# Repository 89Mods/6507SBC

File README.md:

# 6507SBC

A 6507-based single-board computer with 128 bytes RAM, 7KiB ROM, I/O, graphics and sound. As an added challenge, it was built with the requirement to not contain any IC larger than DIP-28.

`Hardware` contains the KiCad project files for the SBC itself, as well as the adapter board for the supported SPI peripherals.

`Programs` are programs written to test various features of the SBC.

`Verilog` contains a basic Verilog implementation of the 6507, and the pixel LCD peripheral. Used during software development when ROM swapping became too tedious. Doesn’t implement undocumented instructions or decimal mode.

For more information, see the writeup [on my website](https://tholin.dev/6507/).

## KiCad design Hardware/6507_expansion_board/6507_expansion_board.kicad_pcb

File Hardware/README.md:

# Hardware

Here are the KiCad projects for the computer! BOMs and Gerbers are in the respective 'production' folder of each KiCad project.

The 'expansion board' is a board that plugs directly into a header on the SBC, and adapts some of its I/O ports to two supported SPI peripherals, which can then be driven in software. One is a 25Qxx flash ROM for additional data storage (7KiB isn’t a lot), and the other a pixel LCD (ST7565), which forms the graphics output of the computer.

They can be found for cheap on AliExpress. I got [this one](https://aliexpress.com/item/1005001621784395.html).

However, in the absence of this, the SBC also has a header for a regular character LCD. If this is not required, components J5, RV1 and R19 can be omitted.

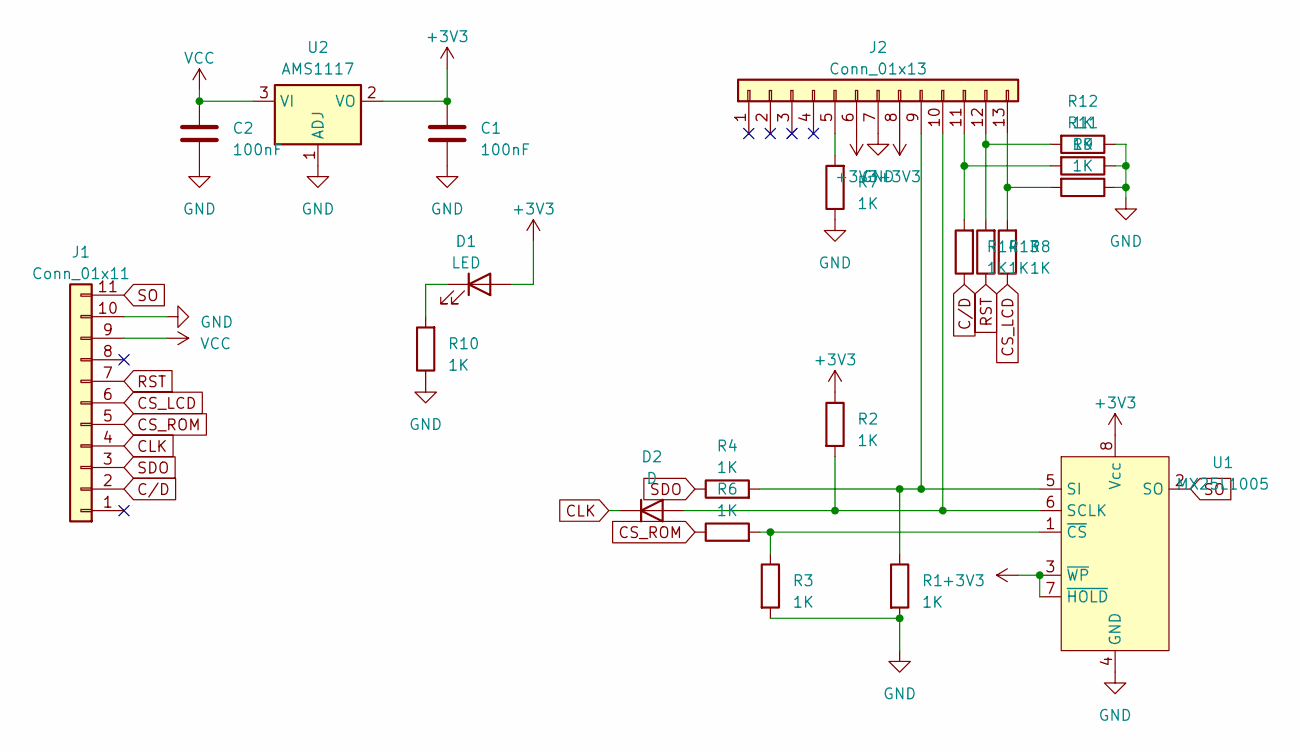
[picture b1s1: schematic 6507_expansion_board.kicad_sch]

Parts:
C1, C2: 100nF; C_1206_3216Metric
D1: LED; LED_0805_2012Metric
D2: D; D_0805_2012Metric
J1: Conn_01x11; PinHeader_1x11_P2.54mm_Vertical
J2: Conn_01x13; PinHeader_1x13_P2.54mm_Vertical
R1, R2, R3, R4, R6, R7, R8, R9, R10, R11, R12, R13, R14: 1K; R_2010_5025Metric_Pad1.40x2.65mm_HandSolder
U1: MX25L1005; DIP-8_W7.62mm_LongPads
U2: AMS1117; SOT-223-3_TabPin2

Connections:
+3V3: C1.1, D1.2 (A), J2.6, J2.8, R2.1, U1.3 (~WP), U1.7 (~HOLD), U1.8 (Vcc), U2.2 (VO)
CLK: D2.1 (K), J1.4
CS_LCD: J1.6, R8.1
CS_ROM: J1.5, R6.1
C/D: J1.2, R14.1
GND: C1.2, C2.2, J1.10, J2.7, R1.2, R3.2, R7.1, R9.1, R10.1, R11.1, R12.1, U1.4 (GND), U2.1 (ADJ)
unnamed: D1.1 (K), R10.2
unnamed: D2.2 (A), J2.10, R2.2, U1.6 (SCLK)
unnamed: J2.5, R7.2
unnamed: J2.9, R1.1, R4.2, U1.5 (SI)
unnamed: J2.11, R11.2, R14.2
unnamed: J2.12, R12.2, R13.2
unnamed: J2.13, R8.2, R9.2
unnamed: R3.1, R6.2, U1.1 (~CS)
RST: J1.7, R13.1
SDO: J1.3, R4.1
SO: J1.11, U1.2 (SO)
VCC: C2.1, J1.9, U2.3 (VI)

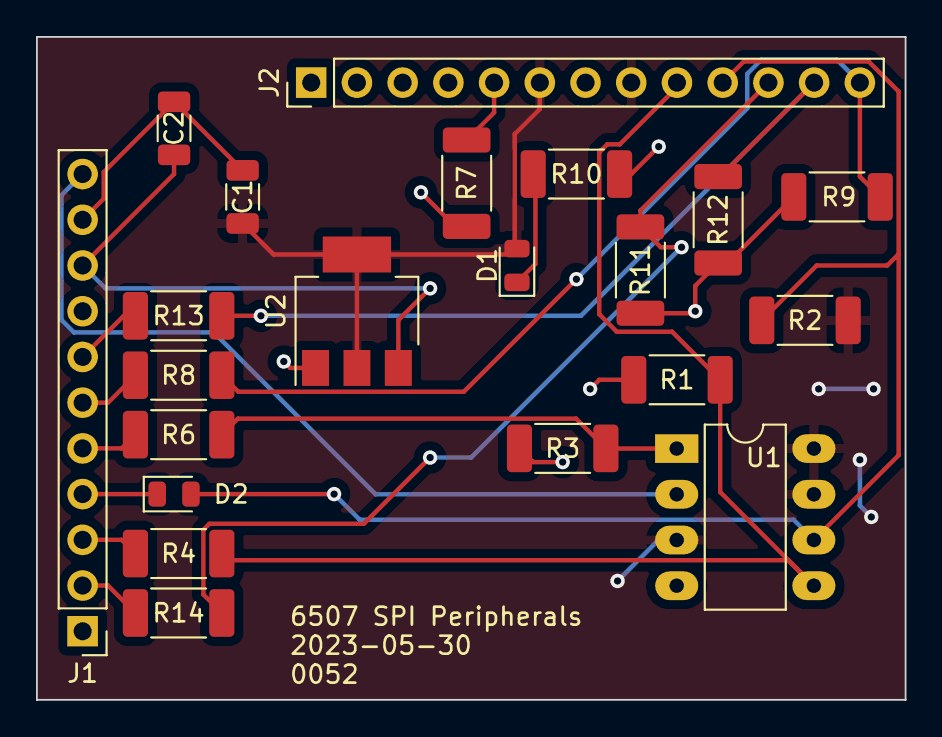
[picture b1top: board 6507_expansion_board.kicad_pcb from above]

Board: 2 copper layers, 48.3 x 36.8 mm, 21 parts (0 on the bottom side), 18 nets.

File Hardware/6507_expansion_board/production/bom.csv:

Designator,Footprint,Quantity,Value,LCSC Part #
C1,1206,1,100nF,
C2,1206,1,100nF,
D1,0805,1,LED,
D2,0805,1,D,
J1,PinHeader_1x11_P2.54mm_Vertical,1,Conn_01x11,
J2,PinHeader_1x13_P2.54mm_Vertical,1,Conn_01x13,
R1,2010,1,1K,
R10,2010,1,1K,
R11,2010,1,1K,
R12,2010,1,1K,
R13,2010,1,1K,
R14,2010,1,1K,
R2,2010,1,1K,
R3,2010,1,1K,
R4,2010,1,1K,
R6,2010,1,1K,
R7,2010,1,1K,
R8,2010,1,1K,
R9,2010,1,1K,
U1,DIP-8_W7.62mm_LongPads,1,MX25L1005,
U2,SOT-223-3_TabPin2,1,AMS1117,

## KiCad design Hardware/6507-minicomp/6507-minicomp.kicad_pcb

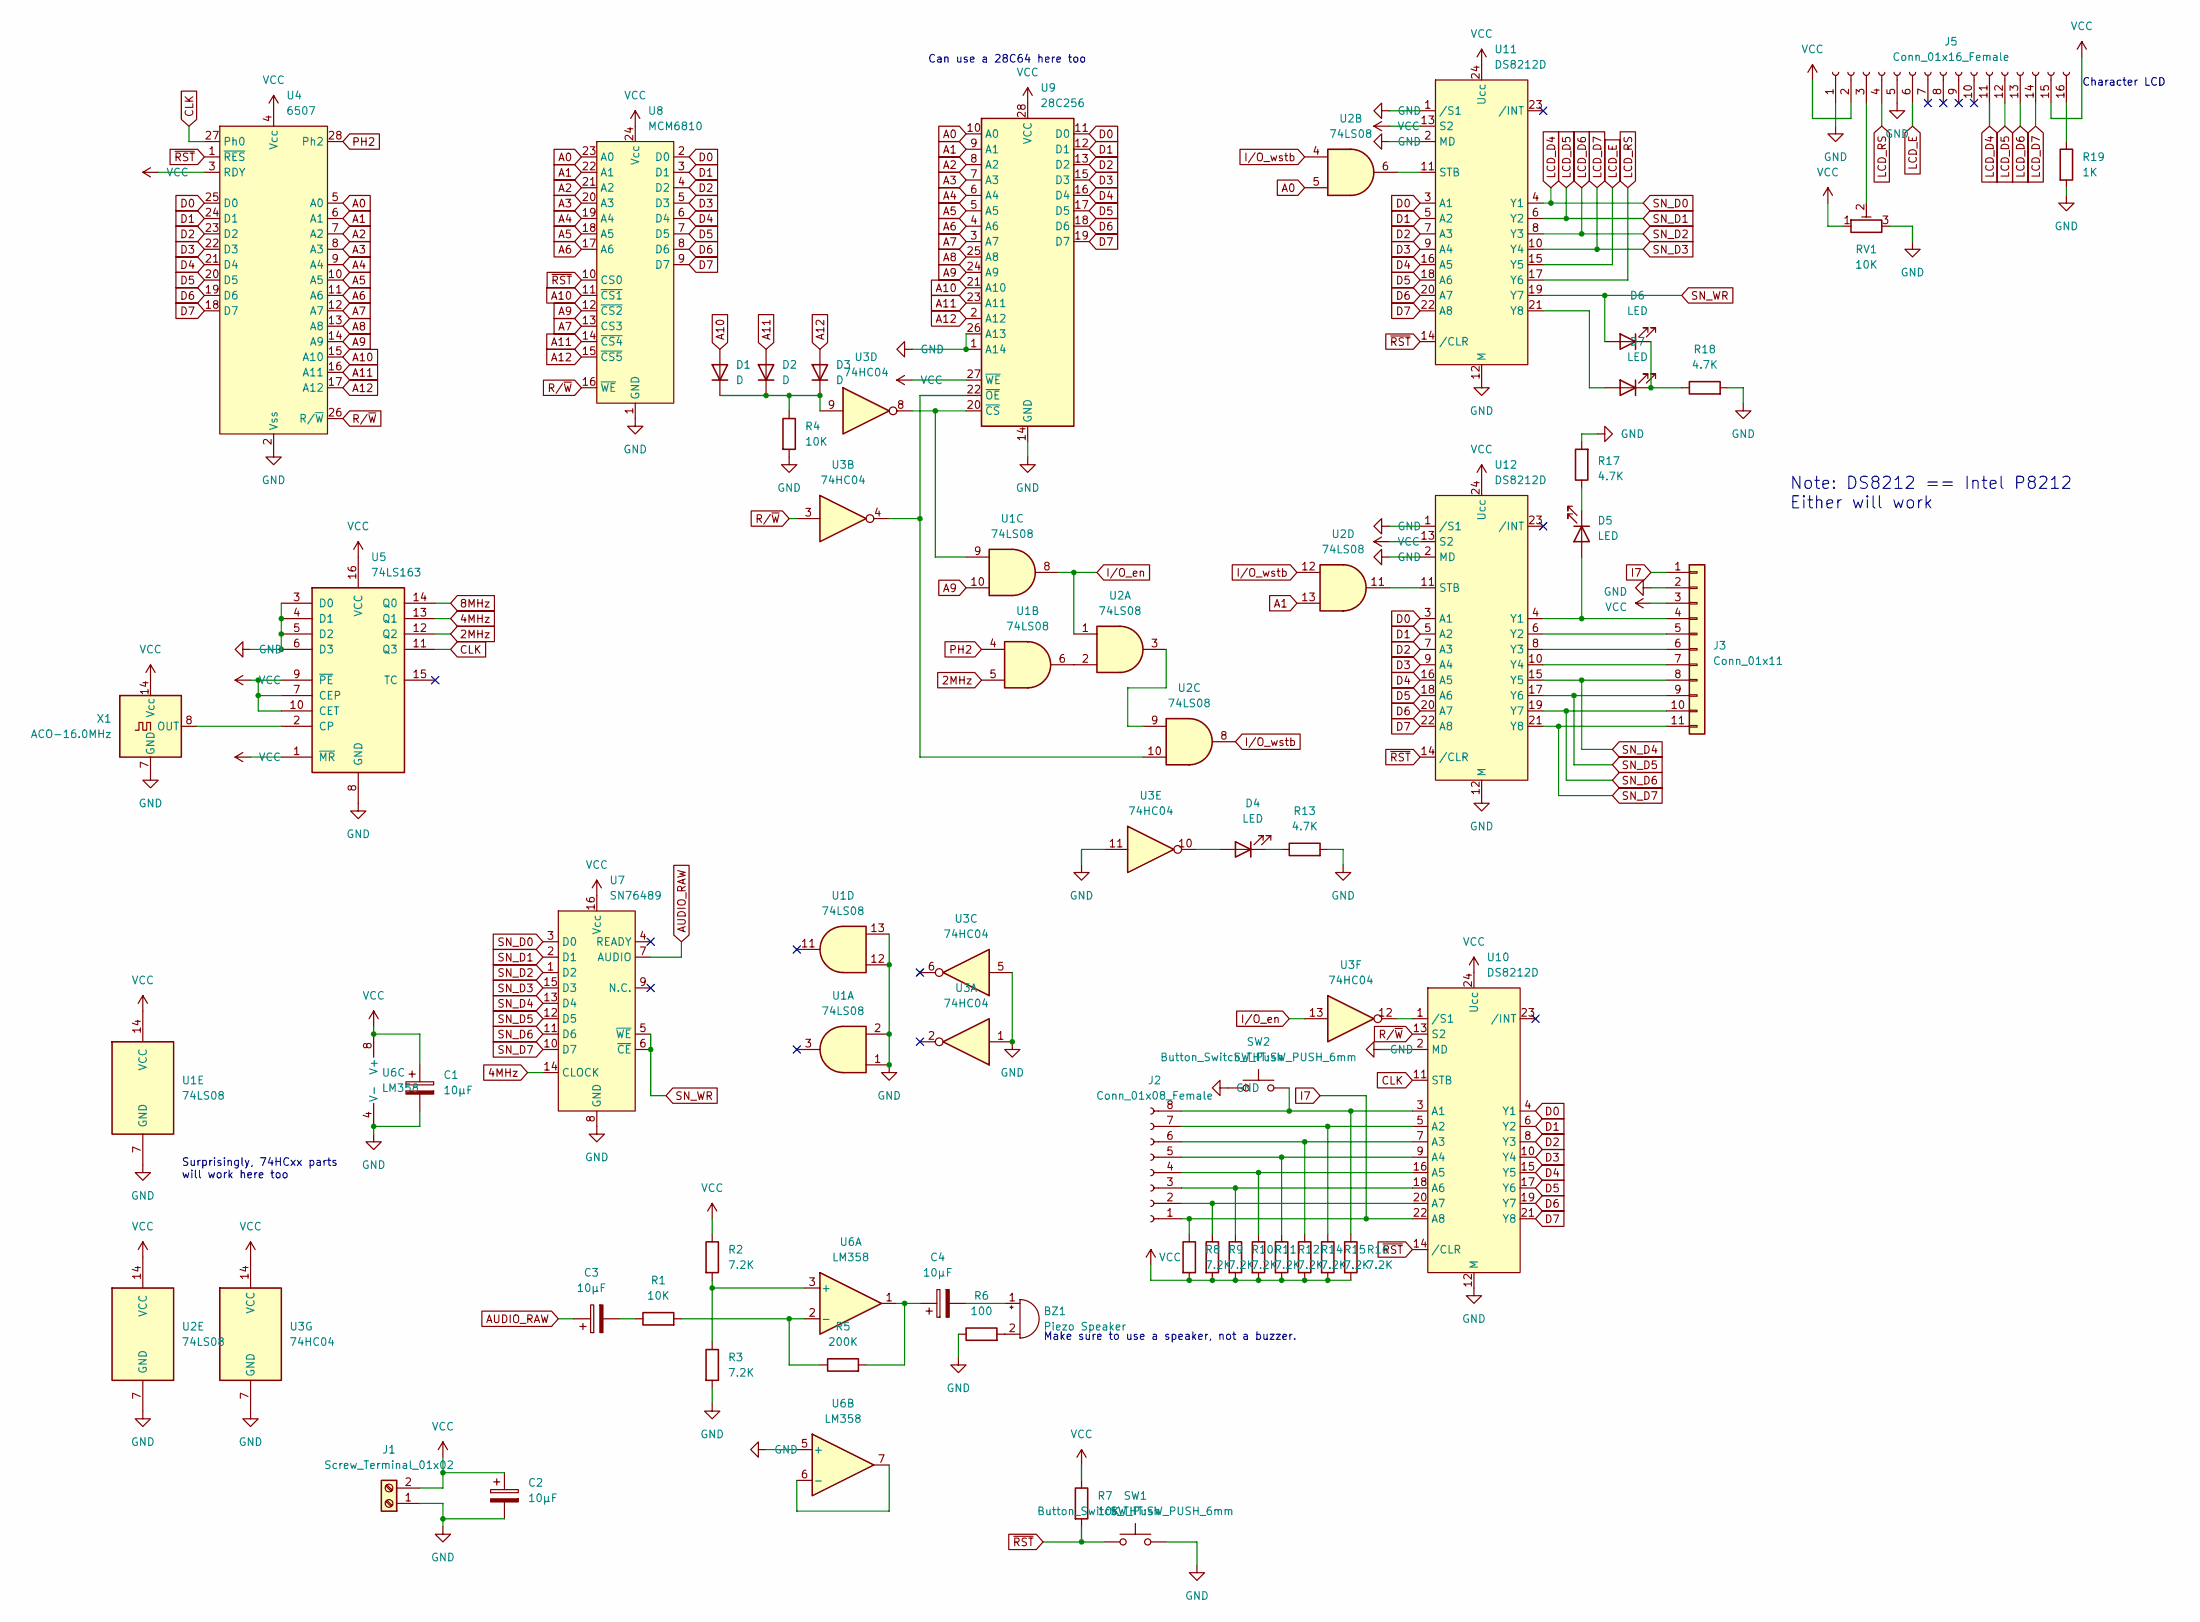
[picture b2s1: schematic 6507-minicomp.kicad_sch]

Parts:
BZ1: Piezo Speaker; Buzzer_12x9.5RM7.6
C1, C2, C3, C4: 10µF; CP_Radial_D6.3mm_P2.50mm
D1, D2, D3: D; D_A-405_P7.62mm_Horizontal
D4, D5, D6, D7: LED; LED_D3.0mm
J1: Screw_Terminal_01x02; TerminalBlock_bornier-2_P5.08mm
J2: Conn_01x08_Female; PinHeader_1x08_P2.54mm_Vertical
J3: Conn_01x11; PinHeader_1x11_P2.54mm_Vertical
J5: Conn_01x16_Female; PinHeader_1x16_P2.54mm_Vertical
R1, R4, R7: 10K; R_Axial_DIN0204_L3.6mm_D1.6mm_P7.62mm_Horizontal
R2, R3, R8, R9, R10, R11, R12, R14, R15, R16: 7.2K; R_Axial_DIN0204_L3.6mm_D1.6mm_P7.62mm_Horizontal
R5: 200K; R_Axial_DIN0204_L3.6mm_D1.6mm_P7.62mm_Horizontal
R6: 100; R_Axial_DIN0204_L3.6mm_D1.6mm_P7.62mm_Horizontal
R13, R17, R18: 4.7K; R_Axial_DIN0204_L3.6mm_D1.6mm_P7.62mm_Horizontal
R19: 1K; R_Axial_DIN0204_L3.6mm_D1.6mm_P7.62mm_Horizontal
RV1: 10K; Potentiometer_ACP_CA9-V10_Vertical
SW1, SW2: SW_Push; SW_PUSH_6mm
U1, U2: 74LS08; DIP-14_W7.62mm
U3: 74HC04; DIP-14_W7.62mm
U4: 6507; DIP-28_W15.24mm
U5: 74LS163; DIP-16_W7.62mm
U6: LM358; DIP-8_W7.62mm
U7: SN76489; DIP-16_W7.62mm
U8: MCM6810; DIP-24_W15.24mm
U9: 28C256; DIP-28_W15.24mm
U10, U11, U12: DS8212D; DIP-24_W15.24mm
X1: ACO-16.0MHz; Oscillator_DIP-14

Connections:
2MHz: U1.5, U5.12 (Q2)
4MHz: U5.13 (Q1), U7.14 (CLOCK)
8MHz: U5.14 (Q0)
A0: U2.5, U4.5 (A0), U8.23 (A0), U9.10 (A0)
A1: U2.13, U4.6 (A1), U8.22 (A1), U9.9 (A1)
A2: U4.7 (A2), U8.21 (A2), U9.8 (A2)
A3: U4.8 (A3), U8.20 (A3), U9.7 (A3)
A4: U4.9 (A4), U8.19 (A4), U9.6 (A4)
A5: U4.10 (A5), U8.18 (A5), U9.5 (A5)
A6: U4.11 (A6), U8.17 (A6), U9.4 (A6)
A7: U4.12 (A7), U8.13 (CS3), U9.3 (A7)
A8: U4.13 (A8), U9.25 (A8)
A9: U1.10, U4.14 (A9), U8.12 (~CS2), U9.24 (A9)
A10: D1.2 (A), U4.15 (A10), U8.11 (~CS1), U9.21 (A10)
A11: D2.2 (A), U4.16 (A11), U8.14 (~CS4), U9.23 (A11)
A12: D3.2 (A), U4.17 (A12), U8.15 (~CS5), U9.2 (A12)
AUDIO_RAW: C3.1, U7.7 (AUDIO)
CLK: U4.27 (Ph0), U5.11 (Q3), U10.11 (STB)
D0: U4.25 (D0), U8.2 (D0), U9.11 (D0), U10.4 (Y1), U11.3 (A1), U12.3 (A1)
D1: U4.24 (D1), U8.3 (D1), U9.12 (D1), U10.6 (Y2), U11.5 (A2), U12.5 (A2)
D2: U4.23 (D2), U8.4 (D2), U9.13 (D2), U10.8 (Y3), U11.7 (A3), U12.7 (A3)
D3: U4.22 (D3), U8.5 (D3), U9.15 (D3), U10.10 (Y4), U11.9 (A4), U12.9 (A4)
D4: U4.21 (D4), U8.6 (D4), U9.16 (D4), U10.15 (Y5), U11.16 (A5), U12.16 (A5)
D5: U4.20 (D5), U8.7 (D5), U9.17 (D5), U10.17 (Y6), U11.18 (A6), U12.18 (A6)
D6: U4.19 (D6), U8.8 (D6), U9.18 (D6), U10.19 (Y7), U11.20 (A7), U12.20 (A7)
D7: U4.18 (D7), U8.9 (D7), U9.19 (D7), U10.21 (Y8), U11.22 (A8), U12.22 (A8)
GND: C1.2, C2.2, J1.1, J3.2, J5.1, J5.5, R3.2, R4.2, R6.1, R13.2, R17.2, R18.2, R19.2, RV1.3, SW1.2, SW2.1, U1.1, U1.2, U1.7 (GND), U1.12, U1.13, U2.7 (GND), U3.1, U3.5, U3.7 (GND), U3.11, U4.2 (Vss), U5.3 (D0), U5.4 (D1), U5.5 (D2), U5.6 (D3), U5.8 (GND), U6.4 (V-), U6.5 (+), U7.8 (GND), U8.1 (GND), U9.1 (A14), U9.14 (GND), U9.26 (A13), U10.2 (MD), U10.12 (M), U11.1 (/S1), U11.2 (MD), U11.12 (M), U12.1 (/S1), U12.2 (MD), U12.12 (M), X1.7 (GND)
I7: J2.1, J3.1, R8.1, U10.22 (A8)
I/O_en: U1.8, U2.1, U3.13
I/O_wstb: U2.4, U2.8, U2.12
LCD_D4: J5.11, U7.3 (D0), U11.4 (Y1)
LCD_D5: J5.12, U7.2 (D1), U11.6 (Y2)
LCD_D6: J5.13, U7.1 (D2), U11.8 (Y3)
LCD_D7: J5.14, U7.15 (D3), U11.10 (Y4)
LCD_E: J5.6, U11.15 (Y5)
LCD_RS: J5.4, U11.17 (Y6)
unnamed: BZ1.2 (+), R6.2
unnamed: BZ1.1 (-), C4.2
unnamed: C3.2, R1.1
unnamed: C4.1, R5.2, U6.1
unnamed: D1.1 (K), D2.1 (K), D3.1 (K), R4.1, U3.9
unnamed: D4.2 (A), U3.10
unnamed: D4.1 (K), R13.1
unnamed: D5.2 (A), J3.4, U12.4 (Y1)
unnamed: D5.1 (K), R17.1
unnamed: D6.1 (K), D7.1 (K), R18.1
unnamed: D7.2 (A), U11.21 (Y8)
unnamed: J2.2, R9.1, U10.20 (A7)
unnamed: J2.3, R10.1, U10.18 (A6)
unnamed: J2.4, R11.1, U10.16 (A5)
unnamed: J2.5, R12.1, U10.9 (A4)
unnamed: J2.6, R14.1, U10.7 (A3)
unnamed: J2.7, R15.1, U10.5 (A2)
unnamed: J2.8, R16.1, SW2.2, U10.3 (A1)
unnamed: J3.5, U12.6 (Y2)
unnamed: J3.6, U12.8 (Y3)
unnamed: J3.7, U12.10 (Y4)
unnamed: J5.3, RV1.2
unnamed: J5.16, R19.1
unnamed: U1.6, U2.2
unnamed: U2.3, U2.9
unnamed: U5.2 (CP), X1.8 (OUT)
unnamed: R2.2, R3.1, U6.3 (+)
unnamed: R1.2, R5.1, U6.2 (-)
unnamed: U6.6 (-), U6.7
unnamed: U1.9, U3.8, U9.20 (~CS)
unnamed: U2.10, U3.4, U9.22 (~OE)
unnamed: U3.12, U10.1 (/S1)
unnamed: U2.6, U11.11 (STB)
unnamed: U2.11, U12.11 (STB)
PH2: U1.4, U4.28 (Ph2)
R/~W: U3.3, U4.26 (R/~W), U8.16 (~WE), U10.13 (S2)
SN_D4: J3.8, U7.13 (D4), U12.15 (Y5)
SN_D5: J3.9, U7.12 (D5), U12.17 (Y6)
SN_D6: J3.10, U7.11 (D6), U12.19 (Y7)
SN_D7: J3.11, U7.10 (D7), U12.21 (Y8)
SN_WR: D6.2 (A), U7.5 (~WE), U7.6 (~CE), U11.19 (Y7)
VCC: C1.1, C2.1, J1.2, J3.3, J5.2, J5.15, R2.1, R7.1, R8.2, R9.2, R10.2, R11.2, R12.2, R14.2, R15.2, R16.2, RV1.1, U1.14 (VCC), U2.14 (VCC), U3.14 (VCC), U4.3 (RDY), U4.4 (Vcc), U5.1 (~MR), U5.7 (CEP), U5.9 (~PE), U5.10 (CET), U5.16 (VCC), U6.8 (V+), U7.16 (Vcc), U8.24 (Vcc), U9.27 (~WE), U9.28 (VCC), U10.24 (Ucc), U11.13 (S2), U11.24 (Ucc), U12.13 (S2), U12.24 (Ucc), X1.14 (Vcc)
~RST: R7.2, SW1.1, U4.1 (~RES), U8.10 (CS0), U10.14 (/CLR), U11.14 (/CLR), U12.14 (/CLR)

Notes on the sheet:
Character LCD
Make sure to use a speaker, not a buzzer.
Note: DS8212 == Intel P8212 Either will work
Surprisingly, 74HCxx parts will work here too
Can use a 28C64 here too

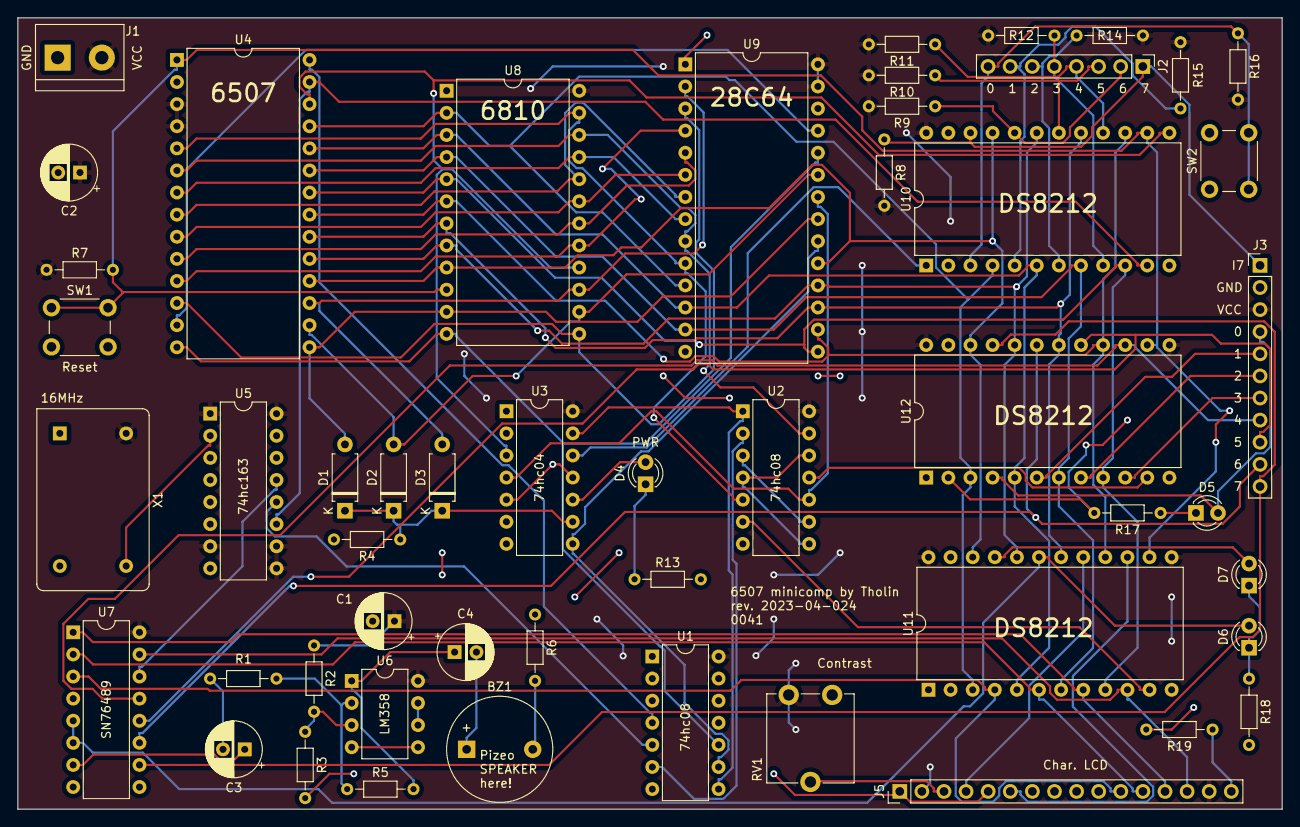
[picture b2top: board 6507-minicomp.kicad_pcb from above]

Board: 2 copper layers, 145.3 x 90.9 mm, 51 parts (0 on the bottom side), 78 nets.

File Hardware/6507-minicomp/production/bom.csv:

Designator,Footprint,Quantity,Value,LCSC Part #
BZ1,Buzzer_12x9.5RM7.6,1,Piezo Speaker,
"C1, C2, C3, C4",CP_Radial_D6.3mm_P2.50mm,4,10µF,
"D1, D2, D3",D_A-405_P7.62mm_Horizontal,3,D,
"D4, D5, D6, D7",LED_D3.0mm,4,LED,
J1,TerminalBlock_bornier-2_P5.08mm,1,Screw_Terminal_01x02,
J2,PinHeader_1x08_P2.54mm_Vertical,1,Conn_01x08_Female,
J3,PinHeader_1x11_P2.54mm_Vertical,1,Conn_01x11,
J5,PinHeader_1x16_P2.54mm_Vertical,1,Conn_01x16_Female,
"R1, R4, R7",R_Axial_DIN0204_L3.6mm_D1.6mm_P7.62mm_Horizontal,3,10K,
"R10, R11, R12, R14, R15, R16, R2, R3, R8, R9",R_Axial_DIN0204_L3.6mm_D1.6mm_P7.62mm_Horizontal,10,7.2K,
"R13, R17, R18",R_Axial_DIN0204_L3.6mm_D1.6mm_P7.62mm_Horizontal,3,4.7K,
R19,R_Axial_DIN0204_L3.6mm_D1.6mm_P7.62mm_Horizontal,1,1K,
R5,R_Axial_DIN0204_L3.6mm_D1.6mm_P7.62mm_Horizontal,1,200K,
R6,R_Axial_DIN0204_L3.6mm_D1.6mm_P7.62mm_Horizontal,1,100,
RV1,Potentiometer_ACP_CA9-V10_Vertical,1,10K,
"SW1, SW2",SW_PUSH_6mm,2,SW_Push,
"U1, U2",DIP-14_W7.62mm,2,74LS08,
"U10, U11, U12",DIP-24_W15.24mm,3,DS8212D,
U3,DIP-14_W7.62mm,1,74HC04,
U4,DIP-28_W15.24mm,1,6507,
U5,DIP-16_W7.62mm,1,74LS163,
U6,DIP-8_W7.62mm,1,LM358,
U7,DIP-16_W7.62mm,1,SN76489,
U8,DIP-24_W15.24mm,1,MCM6810,
U9,DIP-28_W15.24mm,1,28C256,
X1,Oscillator_DIP-14,1,ACO-16.0MHz,

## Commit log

2023-07-06 Initial commit: hardware.
2023-07-06 Verilog and Programs
2023-07-07 READMEs
